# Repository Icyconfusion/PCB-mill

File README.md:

# PCB-mill
A small cnc machine for milling FR4 pcbs using an arduino UNO. It is also capable of CNC engraving at low Z travels. You could potentially do laser engraving if you added a laser to it.

**Note to reveiwer:** I have exported the assembly as .STEP, but I had trouble so there is a zipped .stl of the assembly just in case the .step doesn't work. Also I am updating my BOM with the current prices (since submission) so it might be slightly different (most are cheaper) from my cart pictures. Thank you :) Also, yes the spindle is the cheapest option (prices are in AUD so 50-60 USD is 75-90 AUD). The spindle I am purchasing also includes PSU.

I created this project as a means to create PCBs quickly at home, removing the time and cost of ordering PCBs online. Now I can make 2 layer PCBs at home on my desk for quick prototyping. It also taught me a few things about routing with power draws. To use the project, you simply stream Gcode to the machine over usb form a computer, and the machine will replicate it.

# **Assembly**

The assembly of the project is made up of a few key components. The idea is a stationary, square base with linear rails making the Y axis. The H frame moves along thiscarrying the X and Z axis. Motion is achieved through leadscrews.

To start assembly, there is the base frame that the whole machine is supported by. 4 2020 300m T slot Aluminium profiles are arranged in a square, with M5 T nuts and 90 degree connectors holding them in place. Two 300mm MGN12 linear rails are attached to the top edge of the profiles using M3 T nuts.

Now onto the H. The H moves back and forth along the linear rails attached before, this is the Y axis. The H moves along the rails by a 3d printed bracket, to attach it to the MGN12H carriage. Use 4 M2 screws to attach each bracket to the carriages, then 4 M5 T nuts to attach profiles to each bracket.

We now have the two pillars of the H. Attach to 2060 profile to the pillars using M5 T nuts and 90 degree connectors. The bottom edge of the 2060 should be roughly 4 cm from the top of the bracket we assembled (Exactness is not needed as Z leveling and the spindle height on the mount will compensate for this). Attach the linear rails as before.

To assemble the gantry, screw on both rear MGN12H carriages, and linear rails. Attach the limit switch and press the bearing into place. Then assemble the spindle plate and slide onto the gantry.

Finally, attach the motor, coupler, nutblock and rod, and then slide onto the H frame. The H frame can now slide onto the base frame rails.

Last steps, attach a bed/spoilboard of wood with M5 T nuts. Screw nutblocks to each Y carriage, then mount all 4 Y axis brackets, and their fixing blocks (plus limit switch on one). Now you can feed the rods through and attach the GT2 gears.

Mount the belt plate, motor and drive gear using M5 T nuts, then attach the pulleys.

Finally, attach the X motor bracket, motor and limit switch. The fixing block attaches to the profile on the other side using the T nuts already installed on it. Now you can feed through the leadscrew and assembly is done.

# **Electronics**
The components required for this project are a PSU, an MCU, a spindle or spindle kit, stepper motors, stepper drivers, and limit switches. For the MCU I decided on an arduino UNO because of its pin availability and GRBL compatibility. To power the UNO, I will use an LM2596 buck converter connected to the VIN pin. The PSU is 24v logic, 200w. Power is introduced to the PCB by screw terminals, and powers the VMOT pin of drivers, and 5v logic through the arduino. The steppers are Nema 17 because of their cheap cost and reliability. Drivers used to control these are A4988, which support 1/16 microstepping (why all MS pins are connected to 5v). The 500w spindle comes as a kit including a mount and dedicated PSU. This kit also has speed control to stop the spindle. I am using standard 3 pin limit switches.

## Schematic

Cirkit designer: https://app.cirkitdesigner.com/project/915723a2-d3f0-4d32-8109-c895c4144bcc

## PCB
The PCB for this project interfaces the power supply, steppers, arduino and endstops. It uses wide traces to deliver power from the PSU screw terminals, and has connectors from leftover pins for future connections.

# **Firmware**
The project uses the GRBL library to command the machine. GRBL is a program that instructs the arduino to respond to G-code, sent by a computer. No modifications to GBRL are required other than tweaking default steps/mm, speed, acceleration etc to the machine. To install, copy the edited firmware folder into Arduino IDE libraries, include it in a sketch, and then flash. **It is installed as a zip.**

# **BOM**

### CAD

|Quantity|Name|Picture|
|--------|----|-------|
| 1 | Spindle plate |  |
| 1 | Gantry plate |  |
| 1 | X motor bracket |  |
| 2 | Y carriage |  |
| 1 | Y bearing bracket with switch |  |
| 3 | Y bearing bracket |  |
| 1 | Belt plate |  |

### PCB

2 layer PCB that is 127x118mm.

### Parts
3x Nema 17 stepper motor

1x Arduino uno

3x A4988 stepper driver

1x 24v 200w PSU

1x 500w Spindle kit

1x LM2596 Buck converter

3x Limit switch

1x V bit

1x Drill bit

1x End mill

1x Collet

6x 300mm 2020 T slot aluminium profile (can do 4x300mm and 2x 200mm, but 6x300mm ended up being cheaper)

1x 300mm 2060 T slot profile

8x 90 degree connector

42x M5 T nut

42x M5 screw

32x M3 screw

32x M3 T nut

1x 100mm T8x8 Leadscrew

3x 300mm T8x8 leadscrew

2x 100mm MGN12 linear rail (with MGN12H carriage)

4x 300mm MGN12 linear rail (with MGN12H carriage)

4x T8x8 nutblock 2mm pitch

2x 5x8mm shaft coupler

1x 5mm bore GT2 timing gear

2x 8mm bore GT2 timing gear

1x GT2 belt (at least 600mm)

2x Toothed GT2 idle pulley

2x Smooth GT2 idle pulley

4x Leadscrew fixing block

1x 16x8x5 bearing

1x spoilboard (any wooden sheet)

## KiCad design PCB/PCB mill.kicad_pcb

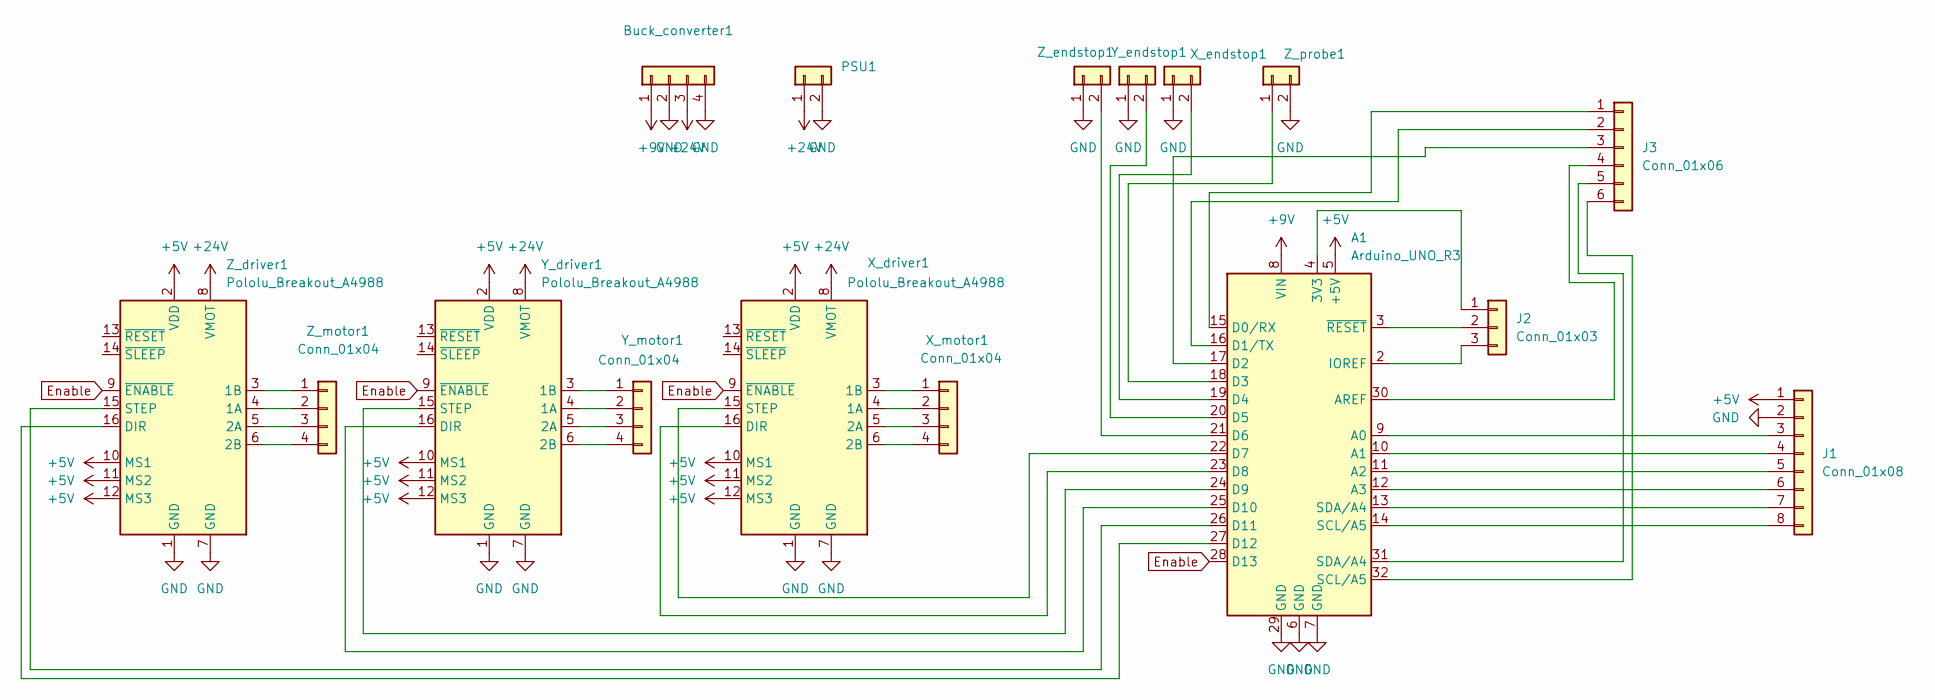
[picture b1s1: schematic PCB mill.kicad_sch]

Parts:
A1: Arduino_UNO_R3
Buck_converter1: Conn_01x04; PinHeader_1x04_P2.54mm_Vertical
J1: Conn_01x08; PinHeader_1x08_P2.54mm_Vertical
J2: Conn_01x03; PinHeader_1x03_P2.54mm_Vertical
J3: Conn_01x06; PinHeader_1x06_P2.54mm_Vertical
PSU1: Conn_01x02; Wuerth_691311400102_P7.62mm
X_driver1: Pololu_Breakout_A4988; Pololu_Breakout-16_15.2x20.3mm
X_endstop1: Conn_01x02; PinHeader_1x02_P2.54mm_Vertical
X_motor1: Conn_01x04; PinHeader_1x04_P2.54mm_Vertical
Y_driver1: Pololu_Breakout_A4988; Pololu_Breakout-16_15.2x20.3mm
Y_endstop1: Conn_01x02; PinHeader_1x02_P2.54mm_Vertical
Y_motor1: Conn_01x04; PinHeader_1x04_P2.54mm_Vertical
Z_driver1: Pololu_Breakout_A4988; Pololu_Breakout-16_15.2x20.3mm
Z_endstop1: Conn_01x02; PinHeader_1x02_P2.54mm_Vertical
Z_motor1: Conn_01x04; PinHeader_1x04_P2.54mm_Vertical
Z_probe1: Conn_01x02; PinHeader_1x02_P2.54mm_Vertical

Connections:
+5V: A1.5 (+5V), J1.1, X_driver1.2 (VDD), X_driver1.10 (MS1), X_driver1.11 (MS2), X_driver1.12 (MS3), Y_driver1.2 (VDD), Y_driver1.10 (MS1), Y_driver1.11 (MS2), Y_driver1.12 (MS3), Z_driver1.2 (VDD), Z_driver1.10 (MS1), Z_driver1.11 (MS2), Z_driver1.12 (MS3)
+9V: A1.8 (VIN), Buck_converter1.1
+24V: Buck_converter1.3, PSU1.1, X_driver1.8 (VMOT), Y_driver1.8 (VMOT), Z_driver1.8 (VMOT)
Enable: A1.28 (D13), X_driver1.9 (~ENABLE), Y_driver1.9 (~ENABLE), Z_driver1.9 (~ENABLE)
GND: A1.6 (GND), A1.7 (GND), A1.29 (GND), Buck_converter1.2, Buck_converter1.4, J1.2, PSU1.2, X_driver1.1 (GND), X_driver1.7 (GND), X_endstop1.1, Y_driver1.1 (GND), Y_driver1.7 (GND), Y_endstop1.1, Z_driver1.1 (GND), Z_driver1.7 (GND), Z_endstop1.1, Z_probe1.2
unnamed: A1.4 (3V3), J2.1
unnamed: A1.9 (A0), J1.3
unnamed: A1.10 (A1), J1.4
unnamed: A1.11 (A2), J1.5
unnamed: A1.12 (A3), J1.6
unnamed: A1.30 (AREF), J3.4
unnamed: A1.15 (D0/RX), J3.1
unnamed: A1.16 (D1/TX), J3.2
unnamed: A1.17 (D2), J3.3
unnamed: A1.18 (D3), Z_probe1.1
unnamed: A1.19 (D4), X_endstop1.2
unnamed: A1.20 (D5), Y_endstop1.2
unnamed: A1.21 (D6), Z_endstop1.2
unnamed: A1.22 (D7), X_driver1.15 (STEP)
unnamed: A1.23 (D8), X_driver1.16 (DIR)
unnamed: A1.24 (D9), Y_driver1.15 (STEP)
unnamed: A1.25 (D10), Y_driver1.16 (DIR)
unnamed: A1.26 (D11), Z_driver1.15 (STEP)
unnamed: A1.27 (D12), Z_driver1.16 (DIR)
unnamed: A1.2 (IOREF), J2.3
unnamed: A1.3 (~RESET), J2.2
unnamed: A1.13 (SDA/A4), J1.7
unnamed: A1.14 (SCL/A5), J1.8
unnamed: A1.31 (SDA/A4), J3.5
unnamed: A1.32 (SCL/A5), J3.6
unnamed: X_driver1.4 (1A), X_motor1.2
unnamed: X_driver1.3 (1B), X_motor1.1
unnamed: X_driver1.5 (2A), X_motor1.3
unnamed: X_driver1.6 (2B), X_motor1.4
unnamed: Y_driver1.4 (1A), Y_motor1.2
unnamed: Y_driver1.3 (1B), Y_motor1.1
unnamed: Y_driver1.5 (2A), Y_motor1.3
unnamed: Y_driver1.6 (2B), Y_motor1.4
unnamed: Z_driver1.4 (1A), Z_motor1.2
unnamed: Z_driver1.3 (1B), Z_motor1.1
unnamed: Z_driver1.5 (2A), Z_motor1.3
unnamed: Z_driver1.6 (2B), Z_motor1.4

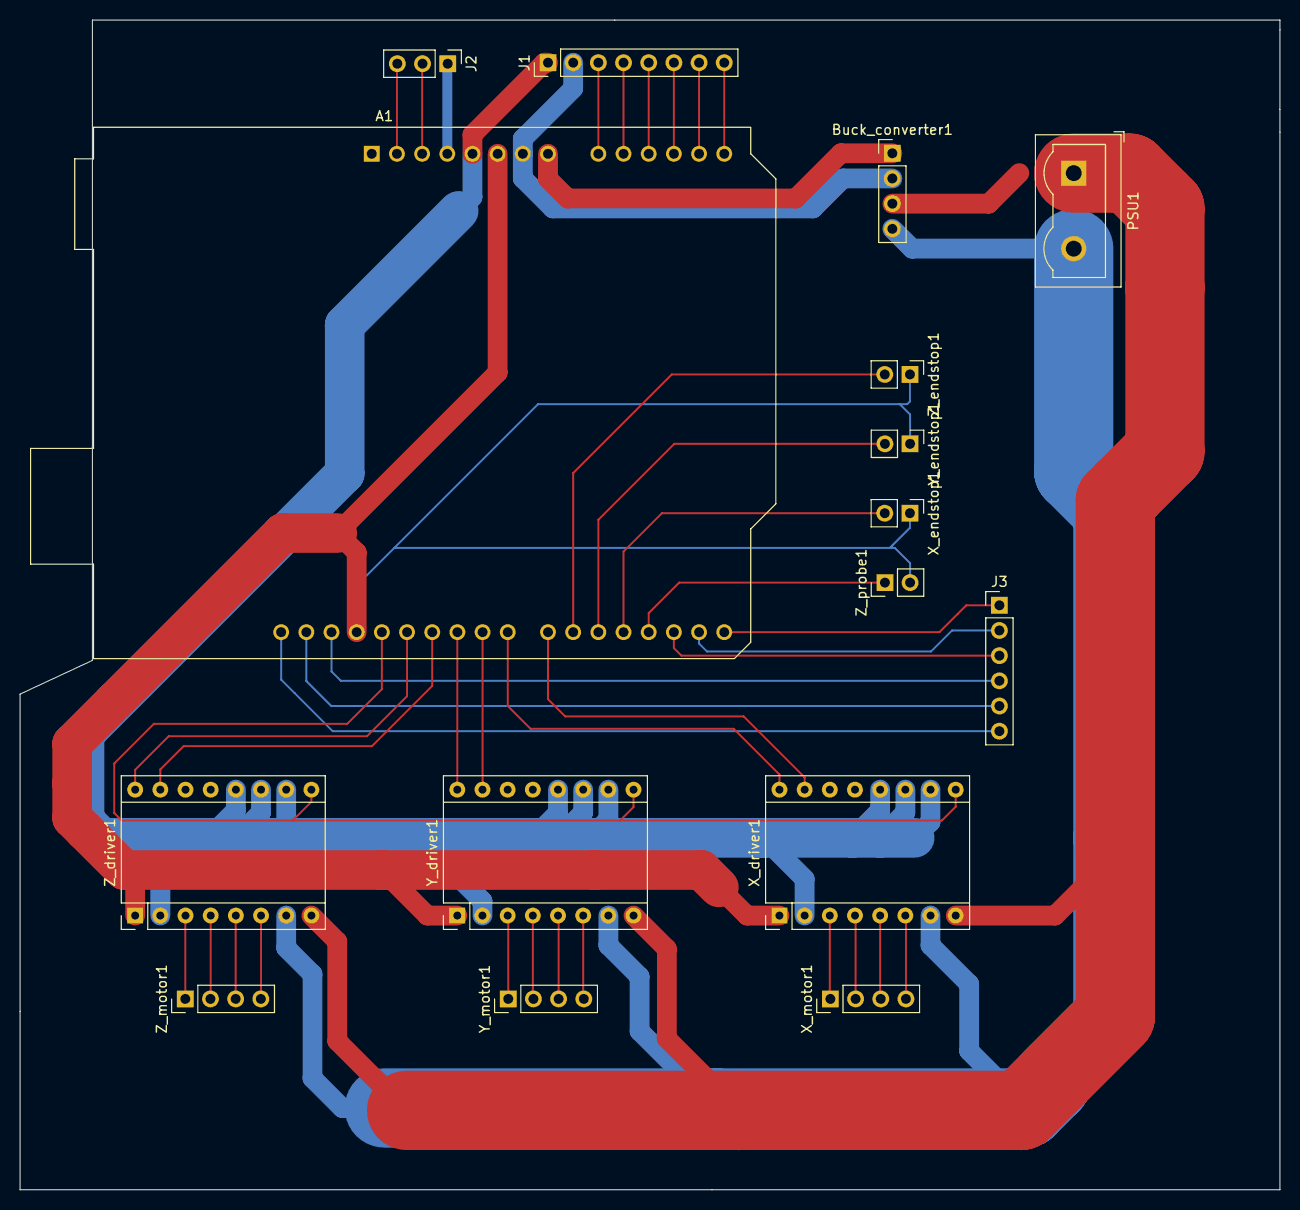
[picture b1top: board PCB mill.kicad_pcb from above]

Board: 2 copper layers, 127.1 x 118.0 mm, 16 parts (0 on the bottom side), 42 nets.

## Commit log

2026-01-22 Rename PCB mill.kicad_prl to PCB/PCB mill.kicad_prl
2026-01-22 Rename PCB mill.kicad_pro to PCB/PCB mill.kicad_pro
2026-01-22 Rename grbl.zip to Firmware/grbl.zip
2026-01-28 Rename Assembly.f3z to CAD/Assembly.f3z
2026-01-28 Rename AssemblySTL.zip to Assembly/AssemblySTL.zip
2026-02-01 Rename Assembly.step to Assembly/Assembly.step
2026-02-18 Rename grblUpload[1].ino to Firmware/grblUpload[1].ino
